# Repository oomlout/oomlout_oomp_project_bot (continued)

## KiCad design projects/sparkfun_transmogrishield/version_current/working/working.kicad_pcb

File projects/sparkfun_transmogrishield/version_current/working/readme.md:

# TransmogriShield by sparkfun  
This is a harvested standardized copy of a project from github.  
The original project can be found at:  
https://github.com/sparkfun/TransmogriShield  
Please consult that link for additional, details, files, and license information.  
Note: It was auto harvested and if the original repo had more than one board file or anything out of the ordinary the files here are likely not representative.

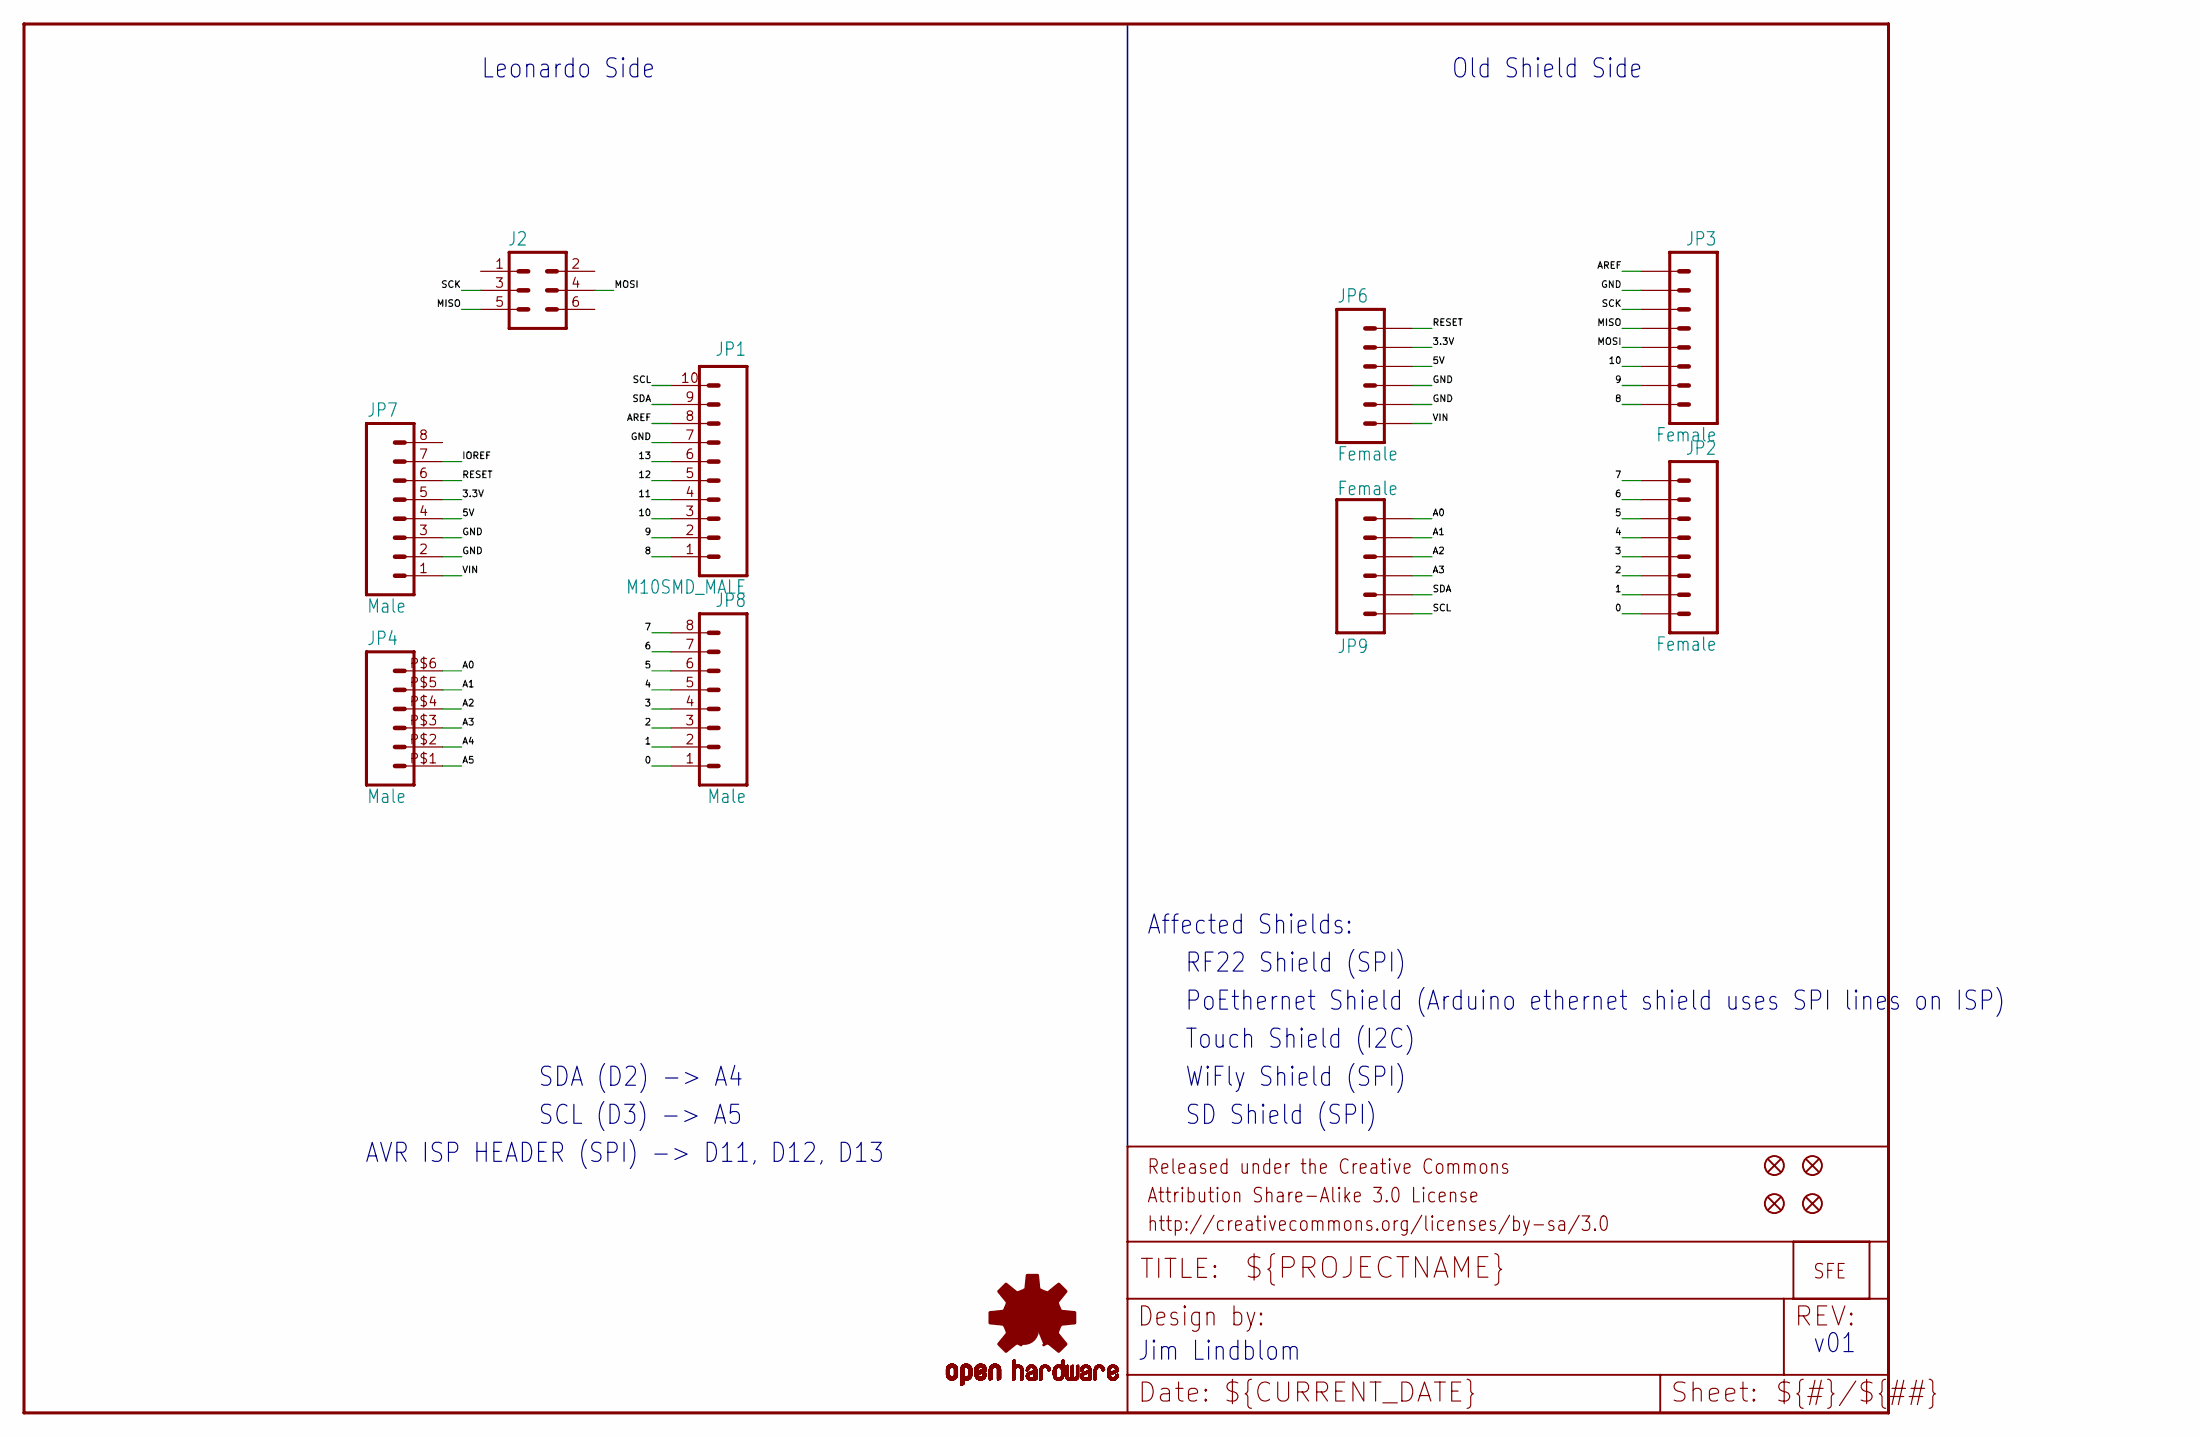
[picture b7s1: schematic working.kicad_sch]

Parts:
J2: M03X2; 2X3_SMD
JP1: M10SMD_MALE; 1X10_SMD_MALE
JP2, JP3: Female; 1X08_SMD_COMBINED
JP4: Male; 1X06_SMD_MALE
JP6, JP9: Female; 1X06_SMD_STRAIGHT_COMBO
JP7, JP8: Male; 1X08_SMD_MALE
JP10: LOGO-SFESK; SFE-LOGO-FLAME
JP11, JP12, JP13, JP14: FIDUCIALUFIDUCIAL; MICRO-FIDUCIAL
U$1: OSHW-LOGOS; OSHW-LOGO-S

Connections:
0: JP2.1, JP2.1@2 (1), JP8.1
1: JP2.2, JP2.2@2 (2), JP8.2
2: JP2.3, JP2.3@2 (3), JP8.3
3: JP2.4, JP2.4@2 (4), JP8.4
3.3V: JP6.5, JP6.5-2 (5), JP7.5
4: JP2.5, JP2.5@2 (5), JP8.5
5: JP2.6, JP2.6@2 (6), JP8.6
5V: JP6.4, JP6.4-2 (4), JP7.4
6: JP2.7, JP2.7@2 (7), JP8.7
7: JP2.8, JP2.8@2 (8), JP8.8
8: JP1.1, JP3.1, JP3.1@2 (1)
9: JP1.2, JP3.2, JP3.2@2 (2)
10: JP1.3, JP3.3, JP3.3@2 (3)
11: JP1.4
12: JP1.5
13: JP1.6
A0: JP4.P$6 (6), JP9.1, JP9.1-2 (1)
A1: JP4.P$5 (5), JP9.2, JP9.2-2 (2)
A2: JP4.P$4 (4), JP9.3, JP9.3-2 (3)
A3: JP4.P$3 (3), JP9.4, JP9.4-2 (4)
A4: JP4.P$2 (2)
A5: JP4.P$1 (1)
AREF: JP1.8, JP3.8, JP3.8@2 (8)
GND: JP1.7, JP3.7, JP3.7@2 (7), JP6.2, JP6.2-2 (2), JP6.3, JP6.3-2 (3), JP7.2, JP7.3
IOREF: JP7.7
MISO: J2.5, JP3.5, JP3.5@2 (5)
MOSI: J2.4, JP3.4, JP3.4@2 (4)
RESET: JP6.6, JP6.6-2 (6), JP7.6
SCK: J2.3, JP3.6, JP3.6@2 (6)
SCL: JP1.10, JP9.6, JP9.6-2 (6)
SDA: JP1.9, JP9.5, JP9.5-2 (5)
VIN: JP6.1, JP6.1-2 (1), JP7.1

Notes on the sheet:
SDA (D2) -> A4
SCL (D3) -> A5
Jim Lindblom
RF22 Shield (SPI)
Leonardo Side
Touch Shield (I2C)
v01
Old Shield Side
Affected Shields:
PoEthernet Shield (Arduino ethernet shield uses SPI lines on ISP)
SD Shield (SPI)
AVR ISP HEADER (SPI) -> D11, D12, D13
WiFly Shield (SPI)

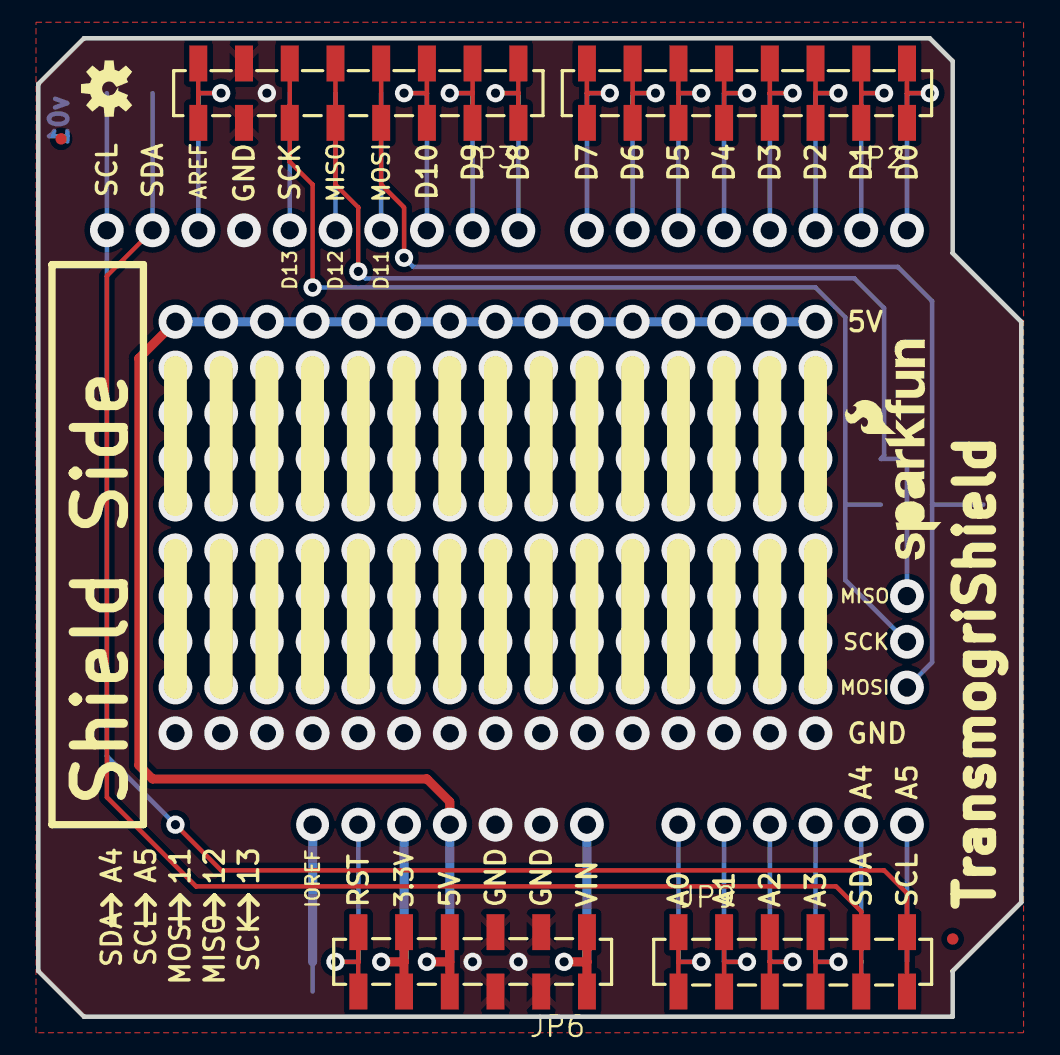
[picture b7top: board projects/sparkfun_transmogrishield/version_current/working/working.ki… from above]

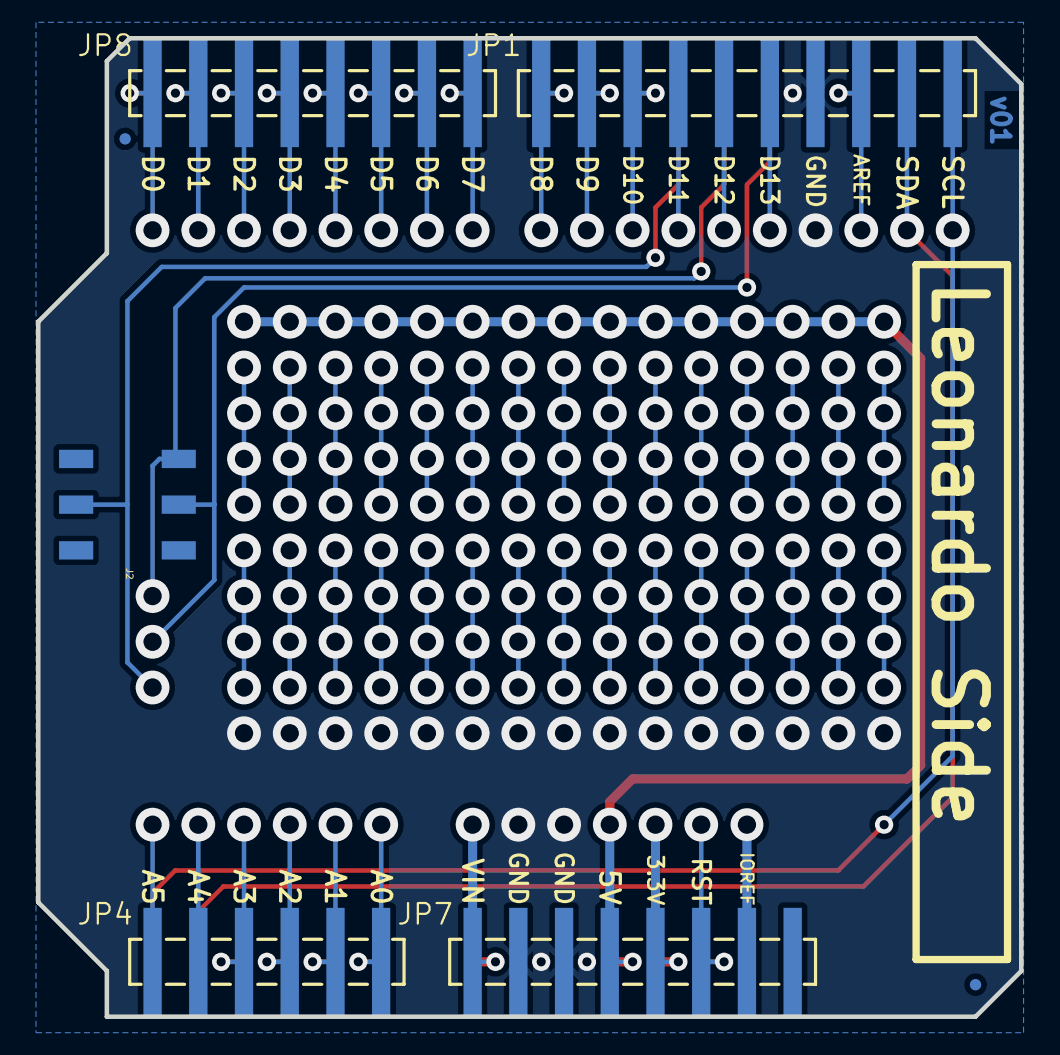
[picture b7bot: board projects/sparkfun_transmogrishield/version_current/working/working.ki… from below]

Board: 2 copper layers, 54.6 x 54.4 mm, 16 parts (7 on the bottom side), 26 nets.

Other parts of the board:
JP5: LOGO-SFENW2; SFE-NEW-WEB

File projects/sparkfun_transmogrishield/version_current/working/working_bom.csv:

"Id";"Designator";"Footprint";"Quantity";"Designation";"Supplier and ref";
1;"JP11,JP12,JP14,JP13";"MICRO-FIDUCIAL";4;"FIDUCIALUFIDUCIAL";;;
2;"JP10";"SFE-LOGO-FLAME";1;"LOGO-SFESK";;;
3;"JP2,JP3";"1X08_SMD_COMBINED";2;"Female";;;
4;"JP5";"SFE-NEW-WEB";1;"LOGO-SFENW2";;;
5;"JP6,JP9";"1X06_SMD_STRAIGHT_COMBO";2;"Female";;;
6;"U$1";"OSHW-LOGO-S";1;"OSHW-LOGOS";;;
7;"JP4";"1X06_SMD_MALE";1;"Male";;;
8;"JP1";"1X10_SMD_MALE";1;"Male";;;
9;"J2";"2X3_SMD";1;"Female";;;
10;"JP7,JP8";"1X08_SMD_MALE";2;"Male";;;

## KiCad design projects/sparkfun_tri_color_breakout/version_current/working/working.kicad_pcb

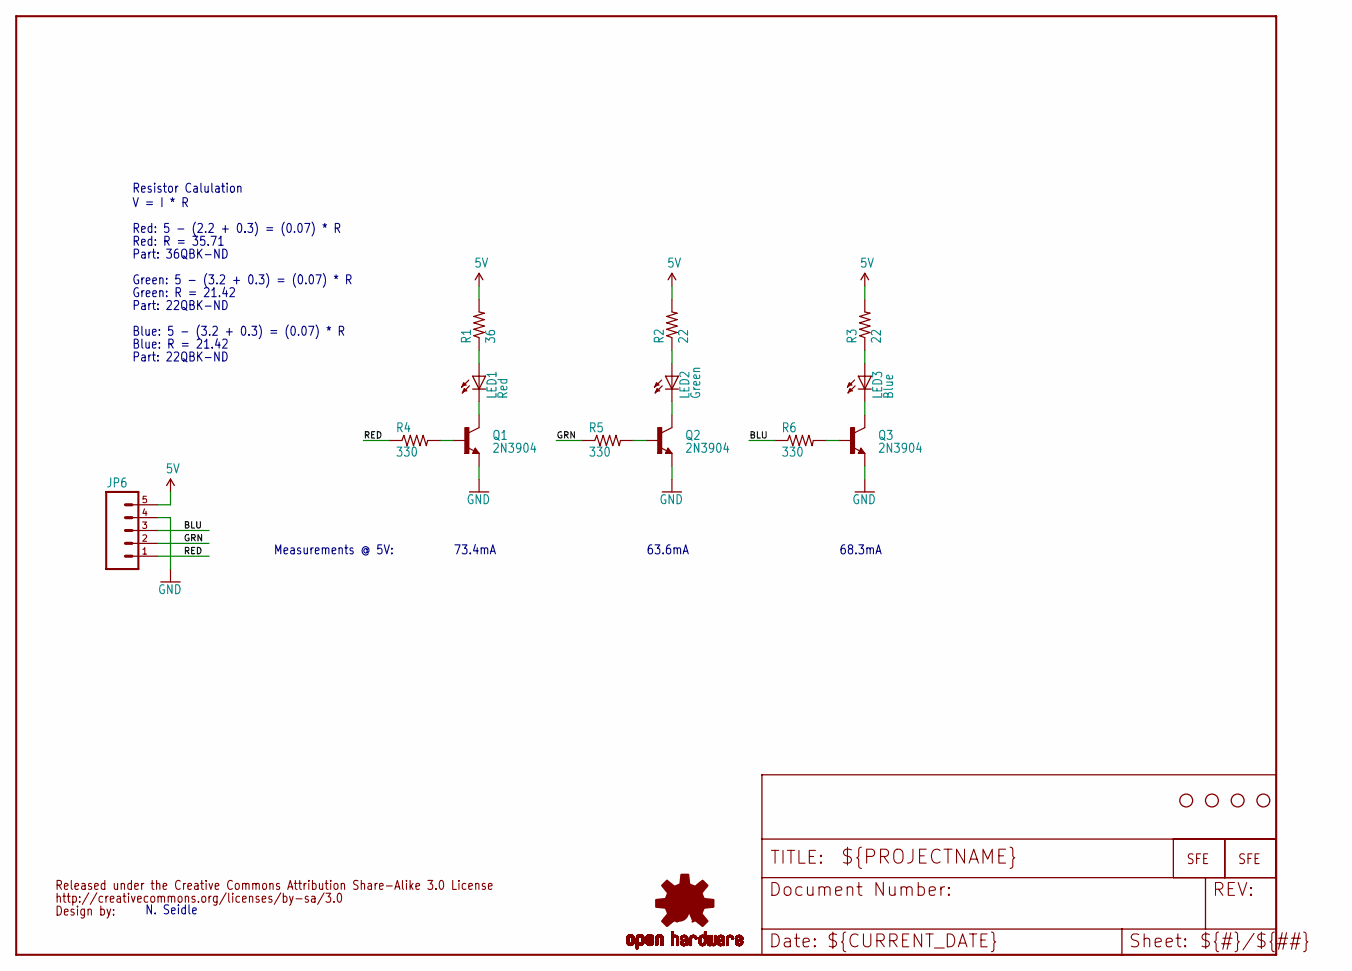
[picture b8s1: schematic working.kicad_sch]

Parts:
JP1, JP2, JP3, JP4: STAND-OFF
JP5, JP7: LOGO-SFESK; SFE-LOGO-FLAME
JP6: M05PTH; 1X05
LED1: Red; LED10MM
LED2: Green; LED10MM
LED3: Blue; LED10MM
Q1, Q2, Q3: 2N3904; TO-92
R1: 36; AXIAL-0.4
R2, R3: 22; AXIAL-0.4
R4, R5, R6: 330; AXIAL-0.3
U$1: CREATIVE_COMMONS
U$6: OSHW-LOGOS; OSHW-LOGO-S

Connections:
5V: JP6.5, R1.P$2 (2), R2.P$2 (2), R3.P$2 (2)
BLU: JP6.3, R6.P$1 (1)
GND: JP6.4, Q1.1 (E), Q2.1 (E), Q3.1 (E)
GRN: JP6.2, R5.P$1 (1)
unnamed: LED2.A, R2.P$1 (1)
unnamed: LED3.A, R3.P$1 (1)
unnamed: LED1.A, R1.P$1 (1)
unnamed: LED1.C, Q1.3 (C)
unnamed: LED2.C, Q2.3 (C)
unnamed: LED3.C, Q3.3 (C)
unnamed: Q1.2 (B), R4.P$2 (2)
unnamed: Q2.2 (B), R5.P$2 (2)
unnamed: Q3.2 (B), R6.P$2 (2)
RED: JP6.1, R4.P$1 (1)

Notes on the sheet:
Blue: 5 - (3.2 + 0.3) = (0.07) * R
Resistor Calulation V = I * R
Measurements @ 5V:
68.3mA
63.6mA
Green: 5 - (3.2 + 0.3) = (0.07) * R
Green: R = 21.42
N. Seidle
Part: 22QBK-ND
Red: 5 - (2.2 + 0.3) = (0.07) * R
Blue: R = 21.42
Red: R = 35.71
Part: 36QBK-ND
73.4mA

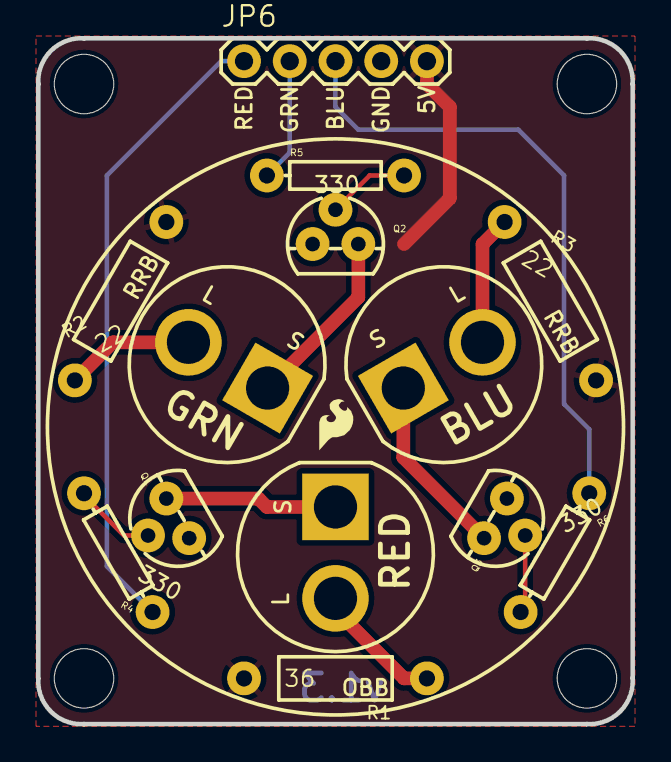
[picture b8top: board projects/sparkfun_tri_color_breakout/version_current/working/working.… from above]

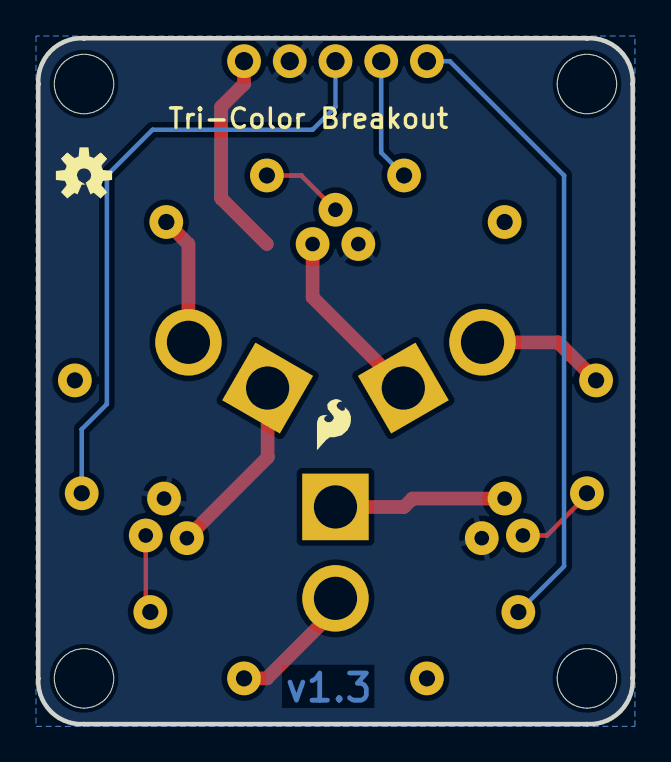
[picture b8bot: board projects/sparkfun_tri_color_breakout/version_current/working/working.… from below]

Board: 2 copper layers, 33.0 x 38.1 mm, 21 parts (2 on the bottom side), 14 nets.

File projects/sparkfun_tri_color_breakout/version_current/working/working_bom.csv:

"Id";"Designator";"Footprint";"Quantity";"Designation";"Supplier and ref";
1;"JP6";"1X05";1;"";;;
2;"LED2";"LED10MM";1;"Green";;;
3;"JP3,JP4,JP2,JP1";"STAND-OFF";4;"STAND-OFF";;;
4;"R4,R6,R5";"AXIAL-0.3";3;"330";;;
5;"R1";"AXIAL-0.4";1;"36";;;
6;"Q2,Q3,Q1";"TO-92";3;"2N3904";;;
7;"LED1";"LED10MM";1;"Red";;;
8;"LED3";"LED10MM";1;"Blue";;;
9;"U$1";"CREATIVE_COMMONS";1;"CREATIVE_COMMONS";;;
10;"JP5,JP7";"SFE-LOGO-FLAME";2;"LOGO-SFESK";;;
11;"R3,R2";"AXIAL-0.4";2;"22";;;
12;"U$6";"OSHW-LOGO-S";1;"OSHW-LOGOS";;;
